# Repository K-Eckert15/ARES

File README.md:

# ARES
ARES capstone with PHOBOS and DEIMOS subsystems

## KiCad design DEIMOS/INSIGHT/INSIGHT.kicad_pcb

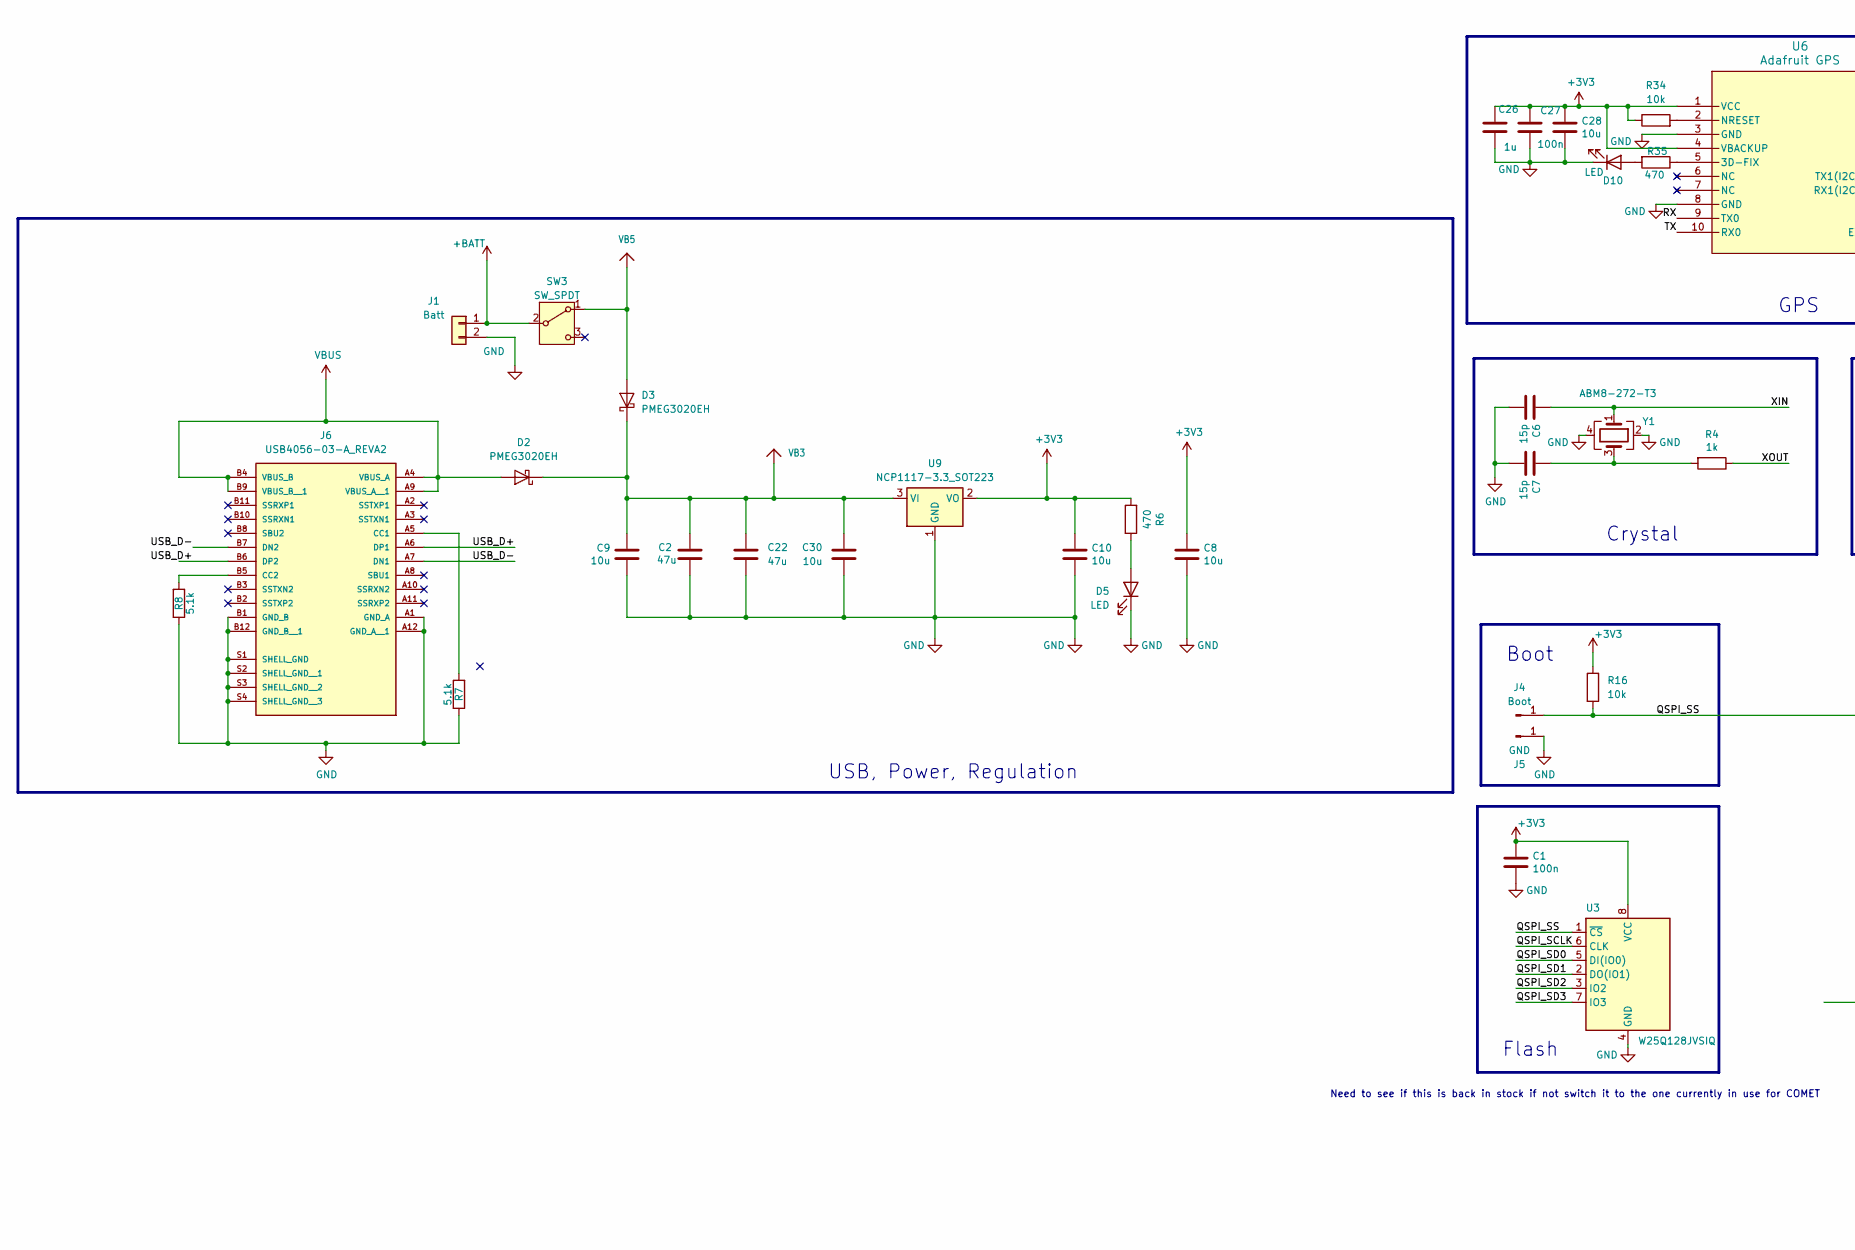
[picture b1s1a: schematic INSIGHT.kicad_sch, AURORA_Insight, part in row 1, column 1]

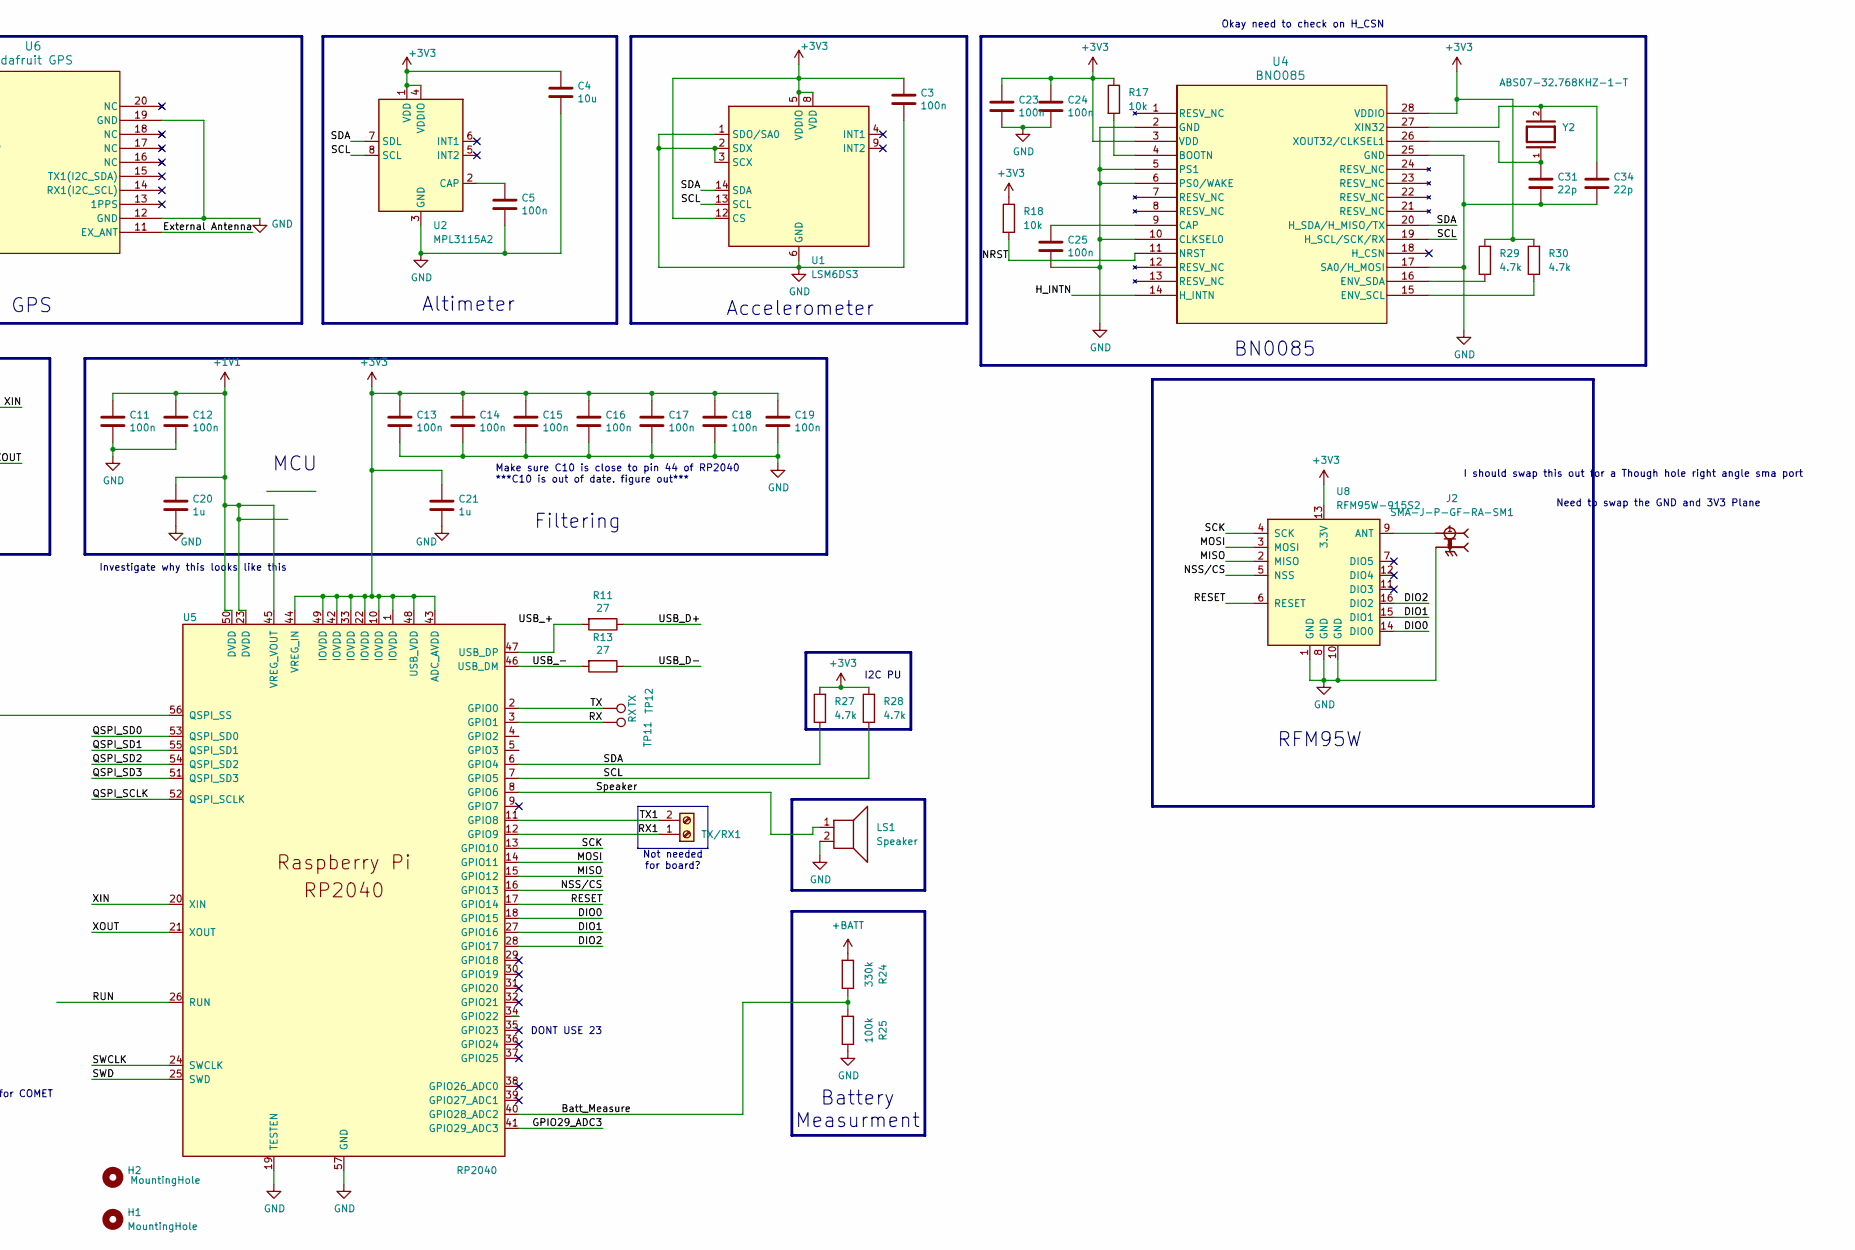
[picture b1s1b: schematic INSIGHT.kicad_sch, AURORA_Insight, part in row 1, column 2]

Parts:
C1, C3, C5, C11, C12, C13, C14, C15, C16, C17, C18, C19, C23, C24, C25, C27: 100n; C_0402_1005Metric
C2: 47u; C_0805_2012Metric_Pad1.18x1.45mm_HandSolder
C4, C8, C9, C10, C28, C30: 10u; C_0603_1608Metric_Pad1.08x0.95mm_HandSolder
C6, C7: 15p; C_0402_1005Metric
C20, C21, C26: 1u; C_0402_1005Metric
C22: 47u; C_1206_3216Metric
C31, C34: 22p; C_0402_1005Metric
D2, D3: PMEG3020EH; D_SOD-123F
D5, D10: LED; LED_0603_1608Metric_Pad1.05x0.95mm_HandSolder
H1, H2: MountingHole; MountingHole_3.2mm_M3_DIN965_Pad
J1: Batt; TerminalBlock_4Ucon_1x02_P3.50mm_Horizontal
J2: SMA-J-P-GF-RA-SM1; SAMTEC_SMA-J-P-GF-RA-SM1; PARTREV D
J4: Boot; TestPoint_Pad_D1.0mm
J5: GND; TestPoint_Pad_D1.0mm
J6: USB4056-03-A_REVA2; GCT_USB4056-03-A_REVA2; PARTREV A2
LS1: Speaker; OWMB-404020SA-40-17
R4: 1k; R_0402_1005Metric
R6, R35: 470; R_0402_1005Metric
R7, R8: 5.1k; R_0402_1005Metric
R11, R13: 27; R_0402_1005Metric
R16, R17, R18, R34: 10k; R_0402_1005Metric
R24: 330k; R_0402_1005Metric
R25: 100k; R_0402_1005Metric
R27, R28, R29, R30: 4.7k; R_0402_1005Metric
SW3: SW_SPDT; SW_SPDT_CK_JS102011SAQN
TP11: RX; TestPoint_THTPad_D1.5mm_Drill0.7mm
TP12: TX; TestPoint_THTPad_D1.5mm_Drill0.7mm
TX/RX1: Screw_Terminal_01x02; TerminalBlock_4Ucon_1x02_P3.50mm_Horizontal
U1: LSM6DS3; LGA-14_3x2.5mm_P0.5mm_LayoutBorder3x4y
U2: MPL3115A2; NXP_LGA-8_3x5mm_P1.25mm_H1.1mm
U3: W25Q128JVSIQ; SOIC-8_5.3x5.3mm_P1.27mm
U4: BNO085; LGA-28_CEV
U5: RP2040; QFN-56-1EP_7x7mm_P0.4mm_EP3.2x3.2mm
U6: Adafruit GPS; CD-PA1616D_ADA
U8: RFM95W-915S2; HOPERF_RFM9XW_SMD
U9: NCP1117-3.3_SOT223; SOT-223-3_TabPin2
Y1: ABM8-272-T3; Crystal_SMD_3225-4Pin_3.2x2.5mm
Y2: ABS07-32.768KHZ-1-T; XTAL_ABS07-32.768KHZ-1-T; PARTREV 08.19.15

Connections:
+1V1: C11.1, C12.1, C20.1, U5.23 (DVDD), U5.45 (VREG_VOUT), U5.50 (DVDD)
+3V3: C1.1, C3.1, C4.1, C8.1, C10.1, C13.1, C14.1, C15.1, C16.1, C17.1, C18.1, C19.1, C21.1, C23.1, C24.1, C26.1, C27.1, C28.1, R6.2, R16.1, R17.1, R18.1, R27.2, R28.2, R29.2, R30.2, R34.1, U1.5 (VDDIO), U1.8 (VDD), U1.12 (CS), U2.1 (VDD), U2.4 (VDDIO), U3.8 (VCC), U4.3 (VDD), U4.28 (VDDIO), U5.1 (IOVDD), U5.10 (IOVDD), U5.22 (IOVDD), U5.33 (IOVDD), U5.42 (IOVDD), U5.43 (ADC_AVDD), U5.44 (VREG_IN), U5.48 (USB_VDD), U5.49 (IOVDD), U6.1 (VCC), U6.4 (VBACKUP), U8.13 (3.3V), U9.2 (VO)
+BATT: J1.1, R24.2, SW3.2 (B)
/Batt_Measure: R24.1, R25.2, U5.40 (GPIO28_ADC2)
/DIO0: U5.18 (GPIO15), U8.14 (DIO0)
/DIO1: U5.27 (GPIO16), U8.15 (DIO1)
/DIO2: U5.28 (GPIO17), U8.16 (DIO2)
/External Antenna: U6.11 (EX_ANT)
/GPIO29_ADC3: U5.41 (GPIO29_ADC3)
/H_INTN: U4.14 (H_INTN)
/MISO: U5.15 (GPIO12), U8.2 (MISO)
/MOSI: U5.14 (GPIO11), U8.3 (MOSI)
/NRST: R18.2, U4.11 (NRST)
/NSS/CS: U5.16 (GPIO13), U8.5 (NSS)
/QSPI_SCLK: U3.6 (CLK), U5.52 (QSPI_SCLK)
/QSPI_SD0: U3.5 (DI(IO0)), U5.53 (QSPI_SD0)
/QSPI_SD1: U3.2 (DO(IO1)), U5.55 (QSPI_SD1)
/QSPI_SD2: U3.3 (IO2), U5.54 (QSPI_SD2)
/QSPI_SD3: U3.7 (IO3), U5.51 (QSPI_SD3)
/QSPI_SS: J4.1 (Pin_1_1), R16.2, U3.1 (~CS), U5.56 (QSPI_SS)
/RESET: U5.17 (GPIO14), U8.6 (RESET)
/RUN: U5.26 (RUN)
/RX: TP11.1, U5.3 (GPIO1), U6.9 (TX0)
/RX1: TX/RX1.1, U5.12 (GPIO9)
/SCK: U5.13 (GPIO10), U8.4 (SCK)
/SCL: R28.1, U1.13 (SCL), U2.8 (SCL), U4.19 (H_SCL/SCK/RX), U5.7 (GPIO5)
/SDA: R27.1, U1.14 (SDA), U2.7 (SDL), U4.20 (H_SDA/H_MISO/TX), U5.6 (GPIO4)
/SWCLK: U5.24 (SWCLK)
/SWD: U5.25 (SWD)
/Speaker: LS1.1, U5.8 (GPIO6)
/TX: TP12.1, U5.2 (GPIO0), U6.10 (RX0)
/TX1: TX/RX1.2, U5.11 (GPIO8)
/USB_+: R11.2, U5.47 (USB_DP)
/USB_-: R13.2, U5.46 (USB_DM)
/USB_D+: J6.A6 (DP1), J6.B6 (DP2), R11.1
/USB_D-: J6.A7 (DN1), J6.B7 (DN2), R13.1
/XIN: C6.1, U5.20 (XIN), Y1.1
/XOUT: R4.1, U5.21 (XOUT)
GND: C1.2, C2.2, C3.2, C4.2, C5.2, C6.2, C7.2, C8.2, C9.2, C10.2, C11.2, C12.2, C13.2, C14.2, C15.2, C16.2, C17.2, C18.2, C19.2, C20.2, C21.2, C22.2, C23.2, C24.2, C25.2, C26.2, C27.2, C28.2, C30.2, C31.2, C34.2, D5.1 (K), D10.1 (K), J1.2, J2.2, J2.3, J2.4, J2.5, J5.1 (Pin_1_1), J6.A1 (GND_A), J6.A12 (GND_A__1), J6.B1 (GND_B), J6.B12 (GND_B__1), J6.S1 (SHELL_GND), J6.S2 (SHELL_GND__1), J6.S3 (SHELL_GND__2), J6.S4 (SHELL_GND__3), LS1.2, R7.1, R8.1, R25.1, U1.1 (SDO/SA0), U1.2 (SDX), U1.3 (SCX), U1.6 (GND), U1.7 (GND), U2.3 (GND), U3.4 (GND), U4.2 (GND), U4.5 (PS1), U4.6 (PS0/WAKE), U4.10 (CLKSEL0), U4.17 (SA0/H_MOSI), U4.25 (GND), U5.19 (TESTEN), U5.57 (GND), U6.3 (GND), U6.8 (GND), U6.12 (GND), U6.19 (GND), U8.1 (GND), U8.8 (GND), U8.10 (GND), U9.1 (GND), Y1.2, Y1.4
unnamed: C7.1, R4.2, Y1.3
unnamed: D5.2 (A), R6.1
unnamed: D10.2 (A), R35.2
unnamed: J6.A5 (CC1), R7.2
unnamed: J6.B5 (CC2), R8.2
unnamed: C5.1, U2.2 (CAP)
unnamed: R17.2, U4.4 (BOOTN)
unnamed: C25.1, U4.9 (CAP)
unnamed: R30.1, U4.15 (ENV_SCL)
unnamed: R29.1, U4.16 (ENV_SDA)
unnamed: C34.1, U4.27 (XIN32), Y2.2
unnamed: C31.1, U4.26 (XOUT32/CLKSEL1), Y2.1
unnamed: R35.1, U6.5 (3D-FIX)
unnamed: R34.2, U6.2 (NRESET)
unnamed: J2.1, U8.9 (ANT)
VB3: C2.1, C9.1, C22.1, C30.1, D2.1 (K), D3.1 (K), U9.3 (VI)
VB5: D3.2 (A), SW3.1 (A)
VBUS: D2.2 (A), J6.A4 (VBUS_A), J6.A9 (VBUS_A__1), J6.B4 (VBUS_B), J6.B9 (VBUS_B__1)

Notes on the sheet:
BN0085
Need to see if this is back in stock if not switch it to the one currently in use for COMET
Accelerometer
Okay need to check on H_CSN
Need to swap the GND and 3V3 Plane
Flash
Make sure C10 is close to pin 44 of RP2040 ***C10 is out of date. figure out***
I2C PU
Not needed for board?
Investigate why this looks like this
Altimeter
Boot
Crystal
Filtering
RFM95W
Battery Measurment
USB, Power, Regulation
DONT USE 23
GPS
I should swap this out for a Though hole right angle sma port
MCU

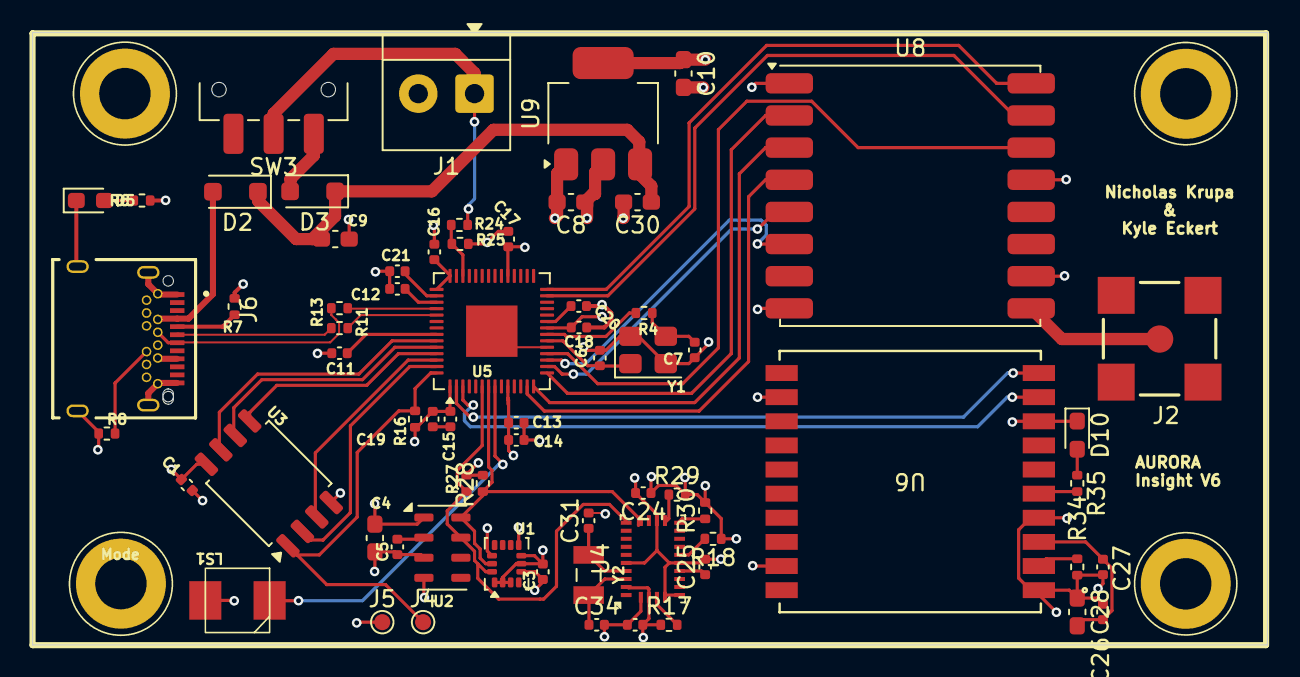
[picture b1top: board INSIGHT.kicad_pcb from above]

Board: 4 copper layers, 76.8 x 38.1 mm, 71 parts (0 on the bottom side), 49 nets.

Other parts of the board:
H2#2, H2#3: MountingHole; MountingHole_3.2mm_M3_DIN965_Pad

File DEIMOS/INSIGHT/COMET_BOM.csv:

"#","Reference","Qty","Value","Exclude from Board","Description","Footprint","List","Notes"
"1","C1,C3,C5,C11,C12,C13,C14,C15,C16,C17,C18,C19,C23,C24,C25,C27","16","100n","","CL05B104KO5NNNC","Capacitor_SMD:C_0402_1005Metric","1",""
"2","C4,C8,C9,C10,C28,C30","6","10u","","GMC10X5R106K25NT","Capacitor_SMD:C_0603_1608Metric_Pad1.08x0.95mm_HandSolder","1","Low ESR,Make sure rated for 12V"
"3","C6,C7","2","15p","","GJM1555C1H150GB01D","Capacitor_SMD:C_0402_1005Metric","1",""
"4","C20,C21,C26","3","1u","","CL05A105KO5NNNC","Capacitor_SMD:C_0402_1005Metric","1",""
"5","C29","1","22u","","GMC10X5R226M16NT","Capacitor_SMD:C_0603_1608Metric_Pad1.08x0.95mm_HandSolder","1",""
"6","C31,C34","2","22p","","GJM1555C1H150GB01D","Capacitor_SMD:C_0402_1005Metric","1",""
"7","D2,D3","2","PMEG3020EH","","30V, 2A ultra low Vf MEGA Schottky barrier rectifier, SOD-123F","Diode_SMD:D_SOD-123F","",""
"8","D5,D10","2","LED","","SML-D12U1WT86","LED_SMD:LED_0603_1608Metric_Pad1.05x0.95mm_HandSolder","1","Red"
"9","J1","1","Batt","","Generic connector, single row, 01x02, script generated (kicad-library-utils/schlib/autogen/connector/)","TerminalBlock_4Ucon:TerminalBlock_4Ucon_1x02_P3.50mm_Horizontal","",""
"10","J2","1","SMA-J-P-GF-RA-SM1","","","SMA-J-P-GF-RA-SM1:SAMTEC_SMA-J-P-GF-RA-SM1","",""
"11","J4","1","Boot","","Generic connector, single row, 01x01, script generated","TestPoint:TestPoint_Pad_D1.0mm","",""
"12","J5","1","GND","","Generic connector, single row, 01x01, script generated","TestPoint:TestPoint_Pad_D1.0mm","",""
"13","J6","1","USB4056-03-A_REVA2","","","USB4056_03_A:GCT_USB4056-03-A_REVA2","",""
"14","LS1","1","Speaker","","OWMB-404020SA-40-17","External/Custom Parts:OWMB-404020SA-40-17","1",""
"15","R1","1","75k","","RG1005P-753-B-T5","Resistor_SMD:R_0402_1005Metric","1",""
"16","R2","1","24k","","CPF0402B24KE1","Resistor_SMD:R_0402_1005Metric","1",""
"17","R3","1","39k","","RP73PF1E39K2BTD","Resistor_SMD:R_0402_1005Metric","1","Actually 39.2k"
"18","R4","1","1k","","AC0402FR-7W1KL","Resistor_SMD:R_0402_1005Metric","1",""
"19","R5,R25","2","100k","","CPF0402B100KE1","Resistor_SMD:R_0402_1005Metric","1",""
"20","R6,R35","2","470","","AC0402FR-7W470RL","Resistor_SMD:R_0402_1005Metric","1",""
"21","R7,R8","2","5.1k","","AC0402FR-7W5K1L","Resistor_SMD:R_0402_1005Metric","1",""
"22","R11,R13","2","27","","RC0402FR-7W27RL","Resistor_SMD:R_0402_1005Metric","1",""
"23","R16,R17,R18,R34","4","10k","","AC0402FR-7W10KL","Resistor_SMD:R_0402_1005Metric","1",""
"24","R24","1","330k","","CRGCQ0402F330K","Resistor_SMD:R_0402_1005Metric","1",""
"25","R27,R28,R29,R30","4","4.7k","","AC0402FR-7W4K7L","Resistor_SMD:R_0402_1005Metric","1",""
"26","SW3","1","SW_SPDT","","500ASSP1SM6QE","Button_Switch_SMD:SW_SPDT_CK_JS102011SAQN","","Add? Shorting Pair?"
"27","U1","1","LSM6DS3","","LSM6DSO32TR","Package_LGA:LGA-14_3x2.5mm_P0.5mm_LayoutBorder3x4y","1","Not In Stock"
"28","U2","1","MPL3115A2","","MPL3115A2ST1","Package_LGA:NXP_LGA-8_3x5mm_P1.25mm_H1.1mm","1","Not In Stock"
"29","U3","1","W25Q128JVSIQ","","W25Q128JVSIQ TR","Package_SO:SOIC-8_5.3x5.3mm_P1.27mm","1",""
"30","U4","1","BNO085","","","footprints:LGA-28_CEV","",""
"31","U5","1","RP2040","","SC0914(13)","Package_DFN_QFN:QFN-56-1EP_7x7mm_P0.4mm_EP3.2x3.2mm","1",""
"32","U6","1","Adafruit GPS","","5186","Library:CD-PA1616D_ADA","1",""
"33","U7","1","MPM3610GQV-Z","","MPM3610GQV-Z","MPM3610:QFN3p0x5p0x1p6_MPM3610_MNP","1","Not In Stock"
"34","U8","1","RFM95W-915S2","","Low power long range transceiver module, SPI and parallel interface, 915 MHz, spreading factor 6 to12, bandwidth 7.8 to 500kHz, -111 to -148 dBm, SMD-16, DIP-16","RF_Module:HOPERF_RFM9XW_SMD","",""
"35","Y1","1","ABM8-272-T3","","ABM8-272-T3","Crystal:Crystal_SMD_3225-4Pin_3.2x2.5mm","1",""
"36","Y2","1","ABS07-32.768KHZ-1-T","","","ABS07_32_768KHZ_1_T:XTAL_ABS07-32.768KHZ-1-T","",""
"37","C2,C22","2","47u","Excluded from board","MAL202135471E3","Capacitor_SMD:C_0805_2012Metric_Pad1.18x1.45mm_HandSolder,Capacitor_SMD:C_1206_3216Metric","","Identify. Found arent rated for 12V"
"38","TX/RX1","1","Screw_Terminal_01x02","Excluded from board","0393570002","TerminalBlock_4Ucon:TerminalBlock_4Ucon_1x02_P3.50mm_Horizontal","","Add?"

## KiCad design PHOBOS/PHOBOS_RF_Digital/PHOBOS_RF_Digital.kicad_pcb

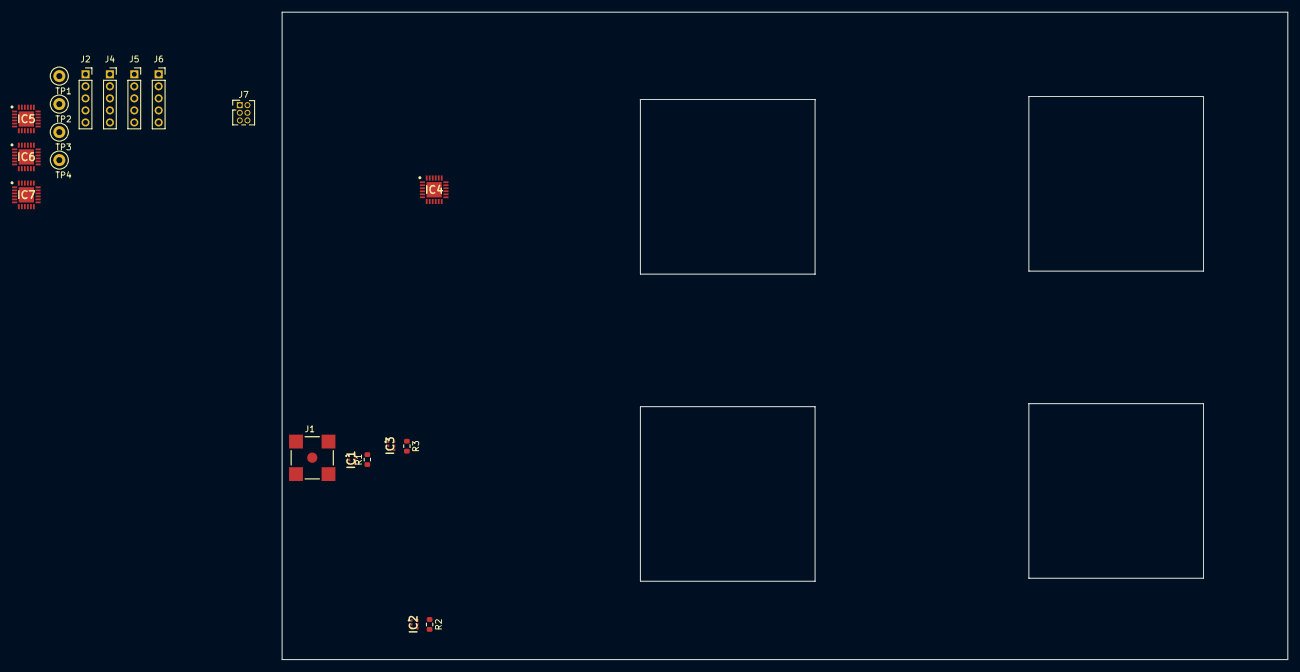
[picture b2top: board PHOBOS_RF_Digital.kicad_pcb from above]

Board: 4 copper layers, 167.0 x 107.5 mm, 20 parts (0 on the bottom side), 27 nets, no tracks yet.

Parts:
IC1, IC2, IC3: PD2328J5050S2HF
IC4, IC5, IC6, IC7: MAPS-010144-TR0500; QFN50P400X400X100-25N-D
J1: RF_IN; SAMTEC_SMA-J-P-GF-RA-SM1
J2: PS1; PinSocket_1x05_P2.00mm_Vertical
J4: PS2; PinSocket_1x05_P2.00mm_Vertical
J5: PS3; PinSocket_1x05_P2.00mm_Vertical
J6: PS4; PinSocket_1x05_P2.00mm_Vertical
J7: PWR; PinHeader_2x03_P1.27mm_Vertical
R1, R2, R3: 100; R_0603_1608Metric
TP1, TP2, TP3, TP4: SER_OUT; TestPoint_Loop_D2.50mm_Drill1.0mm

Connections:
+3V3: IC4.2 (P/S), IC4.18 (VCC), IC5.2 (P/S), IC5.18 (VCC), IC6.2 (P/S), IC6.18 (VCC), IC7.2 (P/S), IC7.18 (VCC), J7.1, J7.2
-3V3: IC4.1 (VEE), IC5.1 (VEE), IC6.1 (VEE), IC7.1 (VEE), J7.3, J7.4
/ANT1: IC4.14 (RF_OUT), IC5.14 (RF_OUT), IC6.14 (RF_OUT), IC7.14 (RF_OUT)
/LE1: IC4.22 (D3/LE), J2.1
/LE2: IC5.22 (D3/LE), J4.1
/LE3: IC6.22 (D3/LE), J5.1
/LE4: IC7.22 (D3/LE), J6.1
/MOSI_1: IC4.24 (D1/SER_IN), J2.3
/MOSI_2: IC5.24 (D1/SER_IN), J4.3
/MOSI_3: IC6.24 (D1/SER_IN), J5.3
/MOSI_4: IC7.24 (D1/SER_IN), J6.3
/PORT1: IC2.4 (OUTPUT1), IC4.5 (RF_IN), R2.1
/PORT2: IC2.6 (OUTPUT2), IC5.5 (RF_IN), R2.2
/PORT3: IC3.4 (OUTPUT1), IC6.5 (RF_IN), R3.1
/PORT4: IC3.6 (OUTPUT2), IC7.5 (RF_IN), R3.2
/RF_IN: IC1.2 (INPUT), J1.1 (In)
/S1_OUT1: IC1.4 (OUTPUT1), IC2.2 (INPUT), R1.1
/S1_OUT2: IC1.6 (OUTPUT2), IC3.2 (INPUT), R1.2
/SCK_1: IC4.23 (D2/CLK), J2.2
/SCK_2: IC5.23 (D2/CLK), J4.2
/SCK_3: IC6.23 (D2/CLK), J5.2
/SCK_4: IC7.23 (D2/CLK), J6.2
GND: IC1.1 (GND_1), IC1.3 (GND_2), IC1.5 (GND_3), IC2.1 (GND_1), IC2.3 (GND_2), IC2.5 (GND_3), IC3.1 (GND_1), IC3.3 (GND_2), IC3.5 (GND_3), IC4.3 (GND_1), IC4.4 (GND_2), IC4.6 (GND_3), IC4.7 (GND_4), IC4.8 (GND_5), IC4.9 (GND_6), IC4.10 (GND_7), IC4.11 (GND_8), IC4.12 (GND_9), IC4.13 (GND_10), IC4.15 (GND_11), IC4.16 (GND_12), IC4.25 (GND_13), IC5.3 (GND_1), IC5.4 (GND_2), IC5.6 (GND_3), IC5.7 (GND_4), IC5.8 (GND_5), IC5.9 (GND_6), IC5.10 (GND_7), IC5.11 (GND_8), IC5.12 (GND_9), IC5.13 (GND_10), IC5.15 (GND_11), IC5.16 (GND_12), IC5.25 (GND_13), IC6.3 (GND_1), IC6.4 (GND_2), IC6.6 (GND_3), IC6.7 (GND_4), IC6.8 (GND_5), IC6.9 (GND_6), IC6.10 (GND_7), IC6.11 (GND_8), IC6.12 (GND_9), IC6.13 (GND_10), IC6.15 (GND_11), IC6.16 (GND_12), IC6.25 (GND_13), IC7.3 (GND_1), IC7.4 (GND_2), IC7.6 (GND_3), IC7.7 (GND_4), IC7.8 (GND_5), IC7.9 (GND_6), IC7.10 (GND_7), IC7.11 (GND_8), IC7.12 (GND_9), IC7.13 (GND_10), IC7.15 (GND_11), IC7.16 (GND_12), IC7.25 (GND_13), J1.2 (Ext), J1.3, J1.4, J1.5, J2.4, J2.5, J4.4, J4.5, J5.4, J5.5, J6.4, J6.5, J7.5, J7.6
unnamed: IC4.17 (SER_OUT), TP1.1 (1_1)
unnamed: IC5.17 (SER_OUT), TP2.1 (1_1)
unnamed: IC6.17 (SER_OUT), TP3.1 (1_1)
unnamed: IC7.17 (SER_OUT), TP4.1 (1_1)

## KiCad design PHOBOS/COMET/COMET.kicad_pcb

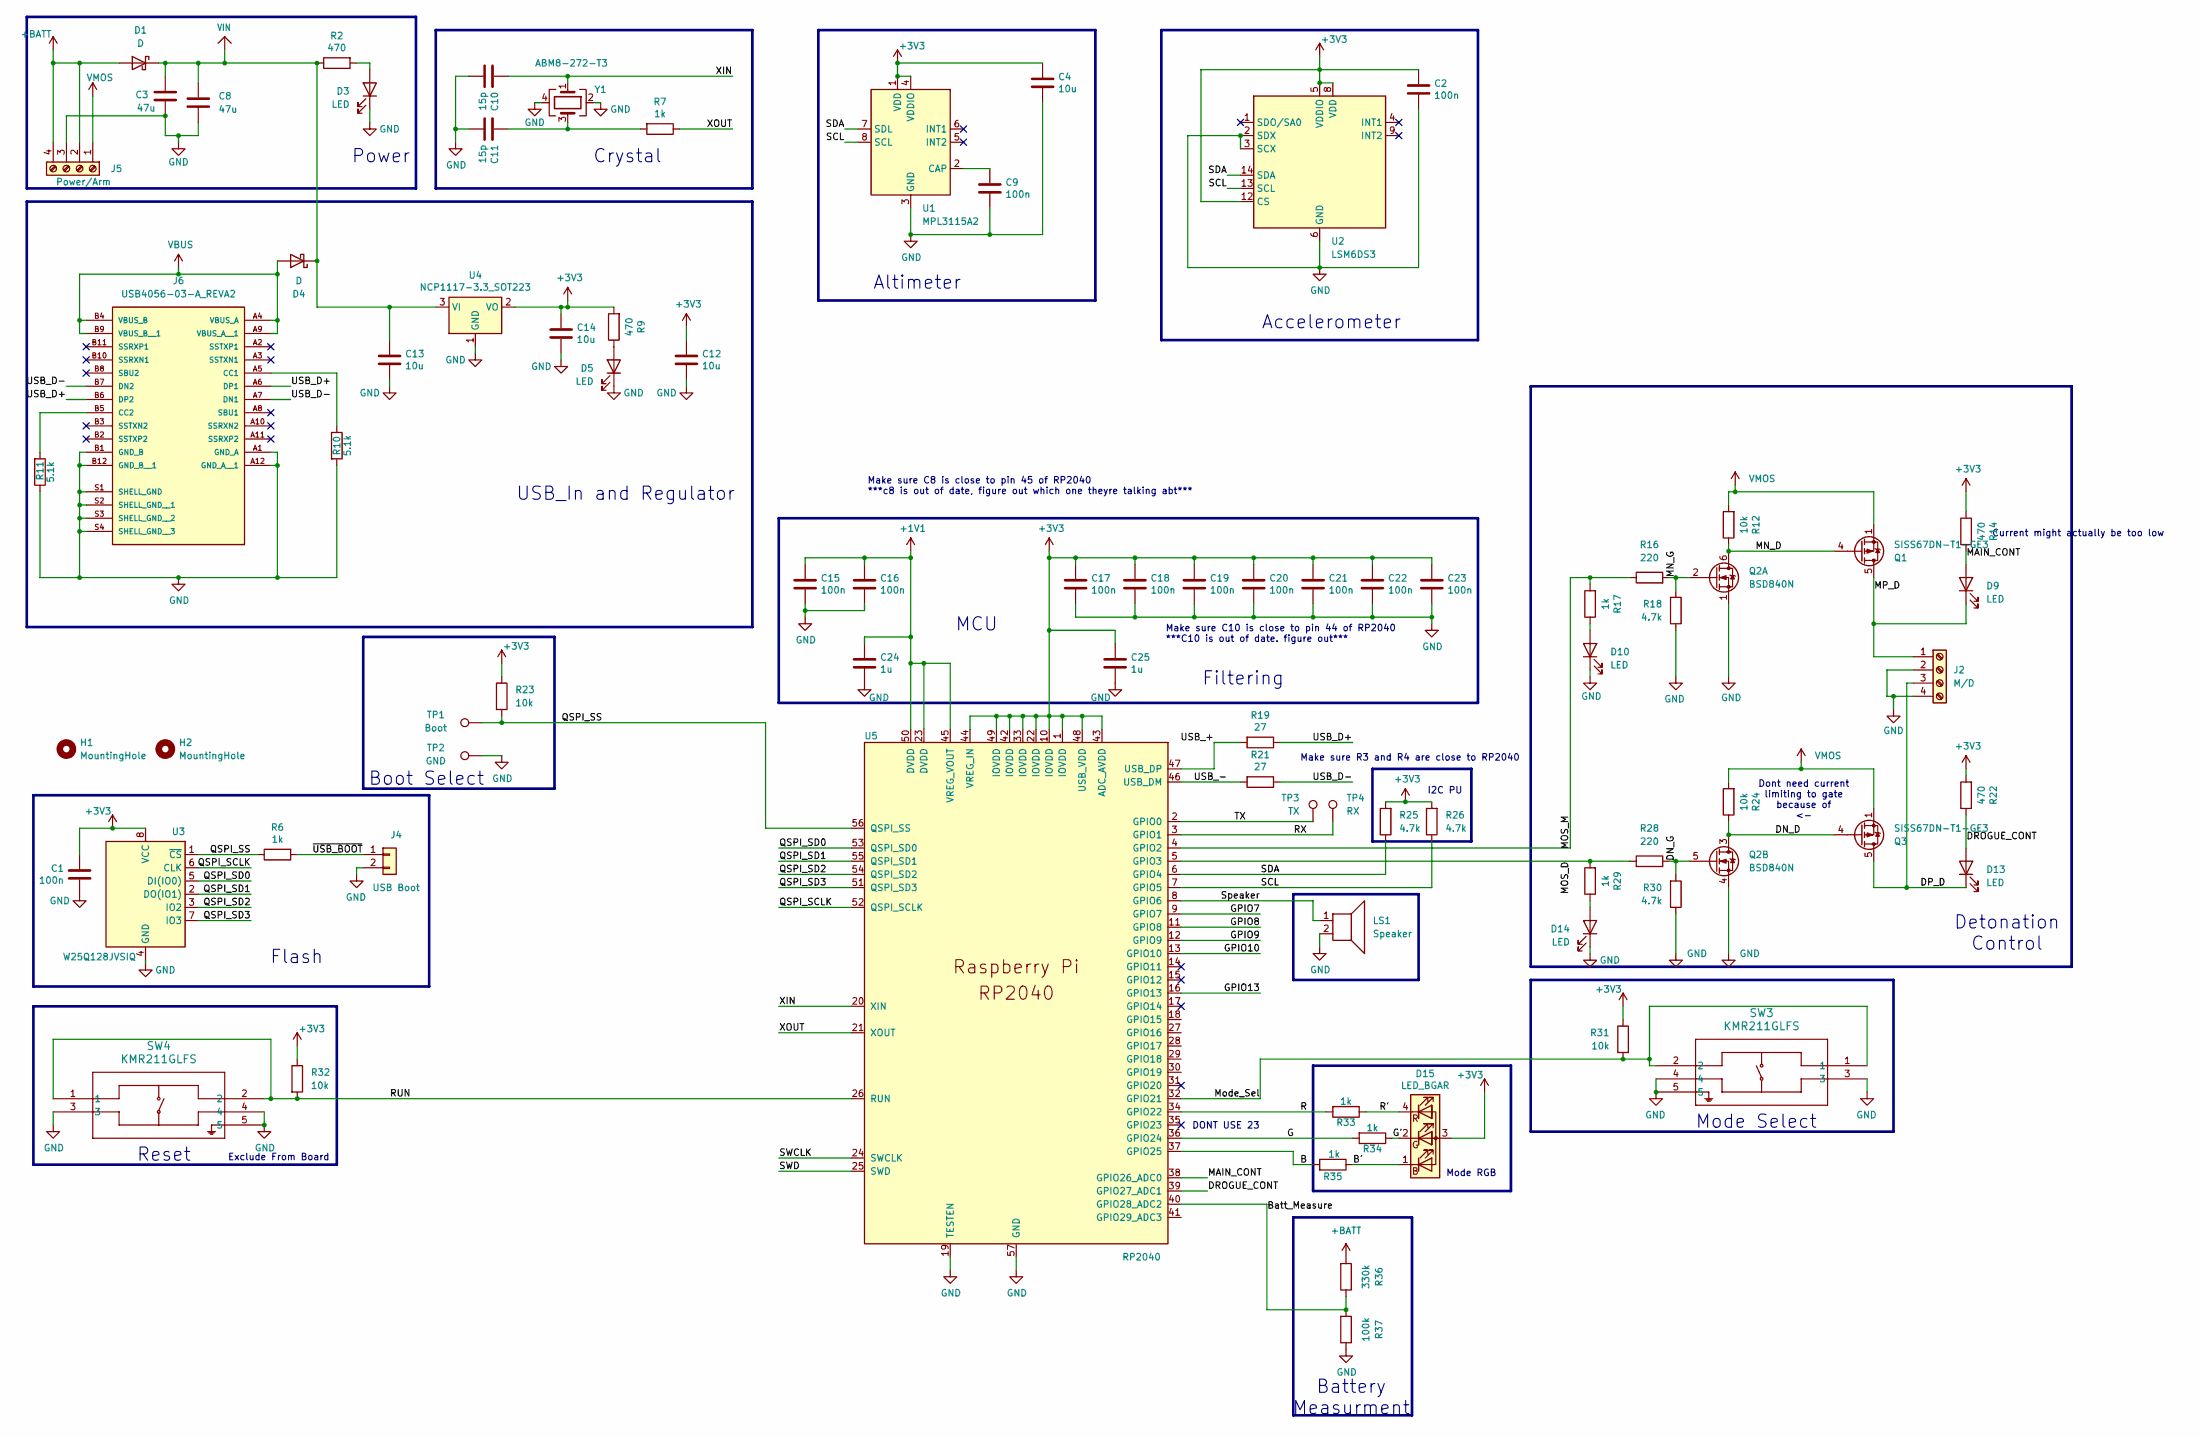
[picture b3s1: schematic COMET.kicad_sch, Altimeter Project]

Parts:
C1, C2, C9, C15, C16, C17, C18, C19, C20, C21, C22, C23: 100n; C_0402_1005Metric; MFG # CL05B104KO5NNNC
C3: 47u; C_0805_2012Metric_Pad1.18x1.45mm_HandSolder; MFG # MAL202135471E3
C4, C12, C13, C14: 10u; C_0603_1608Metric_Pad1.08x0.95mm_HandSolder; MFG # CL10X106MO8NRNC
C8: 47u; C_1206_3216Metric; MFG # MAL202135471E3
C10, C11: 15p; C_0402_1005Metric; MFG # GJM1555C1H150GB01D
C24, C25: 1u; C_0402_1005Metric; MFG # CL05A105KO5NNNC
D1, D4: D; D_0603_1608Metric_Pad1.05x0.95mm_HandSolder; MFG # CD0603-B0340R
D3: LED; LED_0603_1608Metric_Pad1.05x0.95mm_HandSolder
D5, D9, D13: LED; LED_0603_1608Metric_Pad1.05x0.95mm_HandSolder; MFG # SML-D12U1WT86
D10, D14: LED; LED_0603_1608Metric_Pad1.05x0.95mm_HandSolder; MFG # QBLP601-IB5-S2897
D15: LED_BGAR; QBLP600L; MFG # QBLP600L
H1, H2: MountingHole; MountingHole_3.2mm_M3
J2: M/D; TerminalBlock_4Ucon_1x04_P3.50mm_Horizontal; MFG # A112370-ND
J4: USB Boot; PinHeader_1x02_P2.54mm_Vertical
J5: Power/Arm; TerminalBlock_4Ucon_1x04_P3.50mm_Horizontal; MFG # A112370-ND
J6: USB4056-03-A_REVA2; GCT_USB4056-03-A_REVA2; PARTREV A2
LS1: Speaker; OWMB-404020SA-40-17; MFG # AT-0927-TT-6-R
Q1, Q3: SISS67DN-T1-GE3; Vishay_PowerPAK_1212-8_Single; MFG # SISS67DN-T1-GE3
Q2: BSD840N; SOT-363_SC-70-6; MFG # PMGD175XNEX
R2: 470; R_0402_1005Metric
R6, R7, R17, R29, R33, R34, R35: 1k; R_0402_1005Metric; MFG # AC0402FR-7W1KL
R9, R14, R22: 470; R_0402_1005Metric; MFG # AC0402FR-7W470RL
R10, R11: 5.1k; R_0402_1005Metric; MFG # AC0402FR-7W5K1L
R12, R23, R24, R31, R32: 10k; R_0402_1005Metric; MFG # AC0402FR-7W10KL
R16, R28: 220; R_0402_1005Metric; MFG # AC0402FR-7W220RL
R18, R25, R26, R30: 4.7k; R_0402_1005Metric; MFG # AC0402FR-7W4K7L
R19, R21: 27; R_0402_1005Metric; MFG # RC0402FR-7W27RL
R36: 330k; R_0402_1005Metric; MFG # CRGCQ0402F330K
R37: 100k; R_0402_1005Metric; MFG # AC0402FR-7W100KL
SW3, SW4: KMR211GLFS; KMR2xxG_CNK; MFG # KMR211G LFS
TP1: Boot; TestPoint_Pad_D1.0mm
TP2: GND; TestPoint_Pad_D1.0mm
TP3: TX; TestPoint_THTPad_D2.0mm_Drill1.0mm
TP4: RX; TestPoint_THTPad_D2.0mm_Drill1.0mm; MFG # USB4056-03-A_REVA2
U1: MPL3115A2; NXP_LGA-8_3x5mm_P1.25mm_H1.1mm; MFG # MPL3115A2ST1
U2: LSM6DS3; LGA-14_3x2.5mm_P0.5mm_LayoutBorder3x4y; MFG # LSM6DSO32TR
U3: W25Q128JVSIQ; SOIC-8_5.3x5.3mm_P1.27mm; MFG # Winbond W25Q128JVSIQ
U4: NCP1117-3.3_SOT223; SOT-223-3_TabPin2; MFG # NCP1117ST33T3G
U5: RP2040; QFN-56-1EP_7x7mm_P0.4mm_EP3.2x3.2mm; MFG # SC0914(13)
Y1: ABM8-272-T3; Crystal_SMD_3225-4Pin_3.2x2.5mm; MFG # ABM8-272-T3

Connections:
+1V1: C15.1, C16.1, C24.1, U5.23 (DVDD), U5.45 (VREG_VOUT), U5.50 (DVDD)
+3V3: C1.1, C2.1, C4.1, C12.1, C14.1, C17.1, C18.1, C19.1, C20.1, C21.1, C22.1, C23.1, C25.1, D15.3 (A), R9.2, R14.1, R22.2, R23.1, R25.2, R26.2, R31.1, R32.1, U1.1 (VDD), U1.4 (VDDIO), U2.5 (VDDIO), U2.8 (VDD), U2.12 (CS), U3.8 (VCC), U4.2 (VO), U5.1 (IOVDD), U5.10 (IOVDD), U5.22 (IOVDD), U5.33 (IOVDD), U5.42 (IOVDD), U5.43 (ADC_AVDD), U5.44 (VREG_IN), U5.48 (USB_VDD), U5.49 (IOVDD)
+BATT: D1.2 (A), J5.2, J5.4, R36.2
/B: R35.2, U5.37 (GPIO25)
/B': D15.1 (BK), R35.1
/Batt_Measure: R36.1, R37.2, U5.40 (GPIO28_ADC2)
/DN_D: Q2.3 (D), Q3.4 (G), R24.1
/DN_G: Q2.5 (G), R28.2, R30.2
/DP_D: D13.1 (K), J2.3, Q3.5 (D)
/DROGUE_CONT: D13.2 (A), R22.1, U5.39 (GPIO27_ADC1)
/G: R34.2, U5.36 (GPIO24)
/G': D15.2 (GK), R34.1
/GPIO7: U5.9 (GPIO7)
/GPIO8: U5.11 (GPIO8)
/GPIO9: U5.12 (GPIO9)
/GPIO10: U5.13 (GPIO10)
/GPIO13: U5.16 (GPIO13)
/MAIN_CONT: D9.2 (A), R14.2, U5.38 (GPIO26_ADC0)
/MN_D: Q1.4 (G), Q2.6 (D), R12.1
/MN_G: Q2.2 (G), R16.2, R18.2
/MOS_D: R28.1, R29.2, U5.5 (GPIO3)
/MOS_M: R16.1, R17.2, U5.4 (GPIO2)
/MP_D: D9.1 (K), J2.1, Q1.5 (D)
/Mode_Sel: R31.2, SW3.1, SW3.2, U5.32 (GPIO21)
/QSPI_SCLK: U3.6 (CLK), U5.52 (QSPI_SCLK)
/QSPI_SD0: U3.5 (DI(IO0)), U5.53 (QSPI_SD0)
/QSPI_SD1: U3.2 (DO(IO1)), U5.55 (QSPI_SD1)
/QSPI_SD2: U3.3 (IO2), U5.54 (QSPI_SD2)
/QSPI_SD3: U3.7 (IO3), U5.51 (QSPI_SD3)
/QSPI_SS: R6.1, R23.2, TP1.1 (1_1), U3.1 (~CS), U5.56 (QSPI_SS)
/R: R33.2, U5.34 (GPIO22)
/R': D15.4 (RK), R33.1
/RUN: R32.2, SW4.1, SW4.2, U5.26 (RUN)
/RX: TP4.1 (1_1), U5.3 (GPIO1)
/SCL: R26.1, U1.8 (SCL), U2.13 (SCL), U5.7 (GPIO5)
/SDA: R25.1, U1.7 (SDL), U2.14 (SDA), U5.6 (GPIO4)
/SWCLK: U5.24 (SWCLK)
/SWD: U5.25 (SWD)
/Speaker: LS1.1, U5.8 (GPIO6)
/TX: TP3.1 (1_1), U5.2 (GPIO0)
/USB_+: R19.2, U5.47 (USB_DP)
/USB_-: R21.2, U5.46 (USB_DM)
/USB_D+: J6.A6 (DP1), J6.B6 (DP2), R19.1
/USB_D-: J6.A7 (DN1), J6.B7 (DN2), R21.1
/XIN: C10.1, U5.20 (XIN), Y1.1
/XOUT: R7.1, U5.21 (XOUT)
GND: C1.2, C2.2, C3.2, C4.2, C8.2, C9.2, C10.2, C11.2, C12.2, C13.2, C14.2, C15.2, C16.2, C17.2, C18.2, C19.2, C20.2, C21.2, C22.2, C23.2, C24.2, C25.2, D3.1 (K), D5.1 (K), D10.1 (K), D14.1 (K), J2.2, J2.4, J4.2, J5.3, J6.A1 (GND_A), J6.A12 (GND_A__1), J6.B1 (GND_B), J6.B12 (GND_B__1), J6.S1 (SHELL_GND), J6.S2 (SHELL_GND__1), J6.S3 (SHELL_GND__2), J6.S4 (SHELL_GND__3), LS1.2, Q2.1 (S), Q2.4 (S), R10.2, R11.1, R18.1, R30.1, R37.1, SW3.3, SW3.4, SW3.5, SW4.3, SW4.4, SW4.5, TP2.1 (1_1), U1.3 (GND), U2.2 (SDX), U2.3 (SCX), U2.6 (GND), U2.7 (GND), U3.4 (GND), U4.1 (GND), U5.19 (TESTEN), U5.57 (GND), Y1.2, Y1.4
unnamed: C11.1, R7.2, Y1.3
unnamed: D3.2 (A), R2.2
unnamed: D5.2 (A), R9.1
unnamed: D10.2 (A), R17.1
unnamed: D14.2 (A), R29.1
unnamed: J4.1, R6.2
unnamed: J6.A5 (CC1), R10.1
unnamed: J6.B5 (CC2), R11.2
unnamed: C9.1, U1.2 (CAP)
VBUS: D4.2 (A), J6.A4 (VBUS_A), J6.A9 (VBUS_A__1), J6.B4 (VBUS_B), J6.B9 (VBUS_B__1)
VIN: C3.1, C8.1, C13.1, D1.1 (K), D4.1 (K), R2.1, U4.3 (VI)
VMOS: J5.1, Q1.1 (S), Q1.2 (S), Q1.3 (S), Q3.1 (S), Q3.2 (S), Q3.3 (S), R12.2, R24.2

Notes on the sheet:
Accelerometer
Mode Select
Flash
Detonation Control
Make sure C8 is close to pin 45 of RP2040 ***c8 is out of date, figure out which one theyre talking abt***
Make sure C10 is close to pin 44 of RP2040 ***C10 is out of date. figure out***
I2C PU
Altimeter
Boot Select
Make sure R3 and R4 are close to RP2040
Crystal
Current might actually be too low
Filtering
Exclude From Board
Power
Mode RGB
Battery Measurment
USB_In and Regulator
DONT USE 23
Reset
MCU
Dont need current limiting to gate because of <-

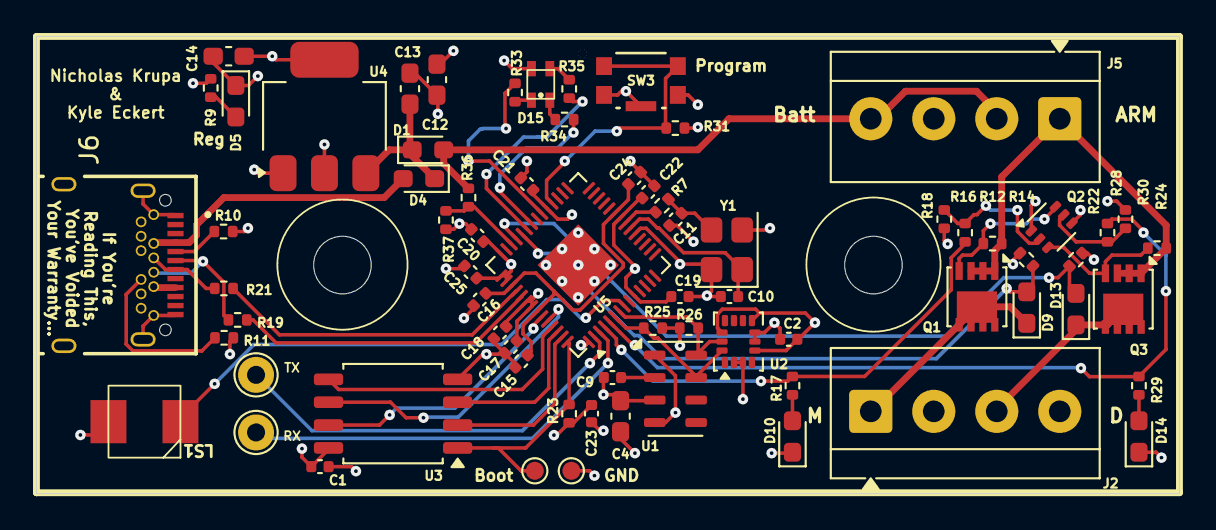
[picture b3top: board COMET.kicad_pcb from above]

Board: 4 copper layers, 63.5 x 25.4 mm, 73 parts (0 on the bottom side), 49 nets.
